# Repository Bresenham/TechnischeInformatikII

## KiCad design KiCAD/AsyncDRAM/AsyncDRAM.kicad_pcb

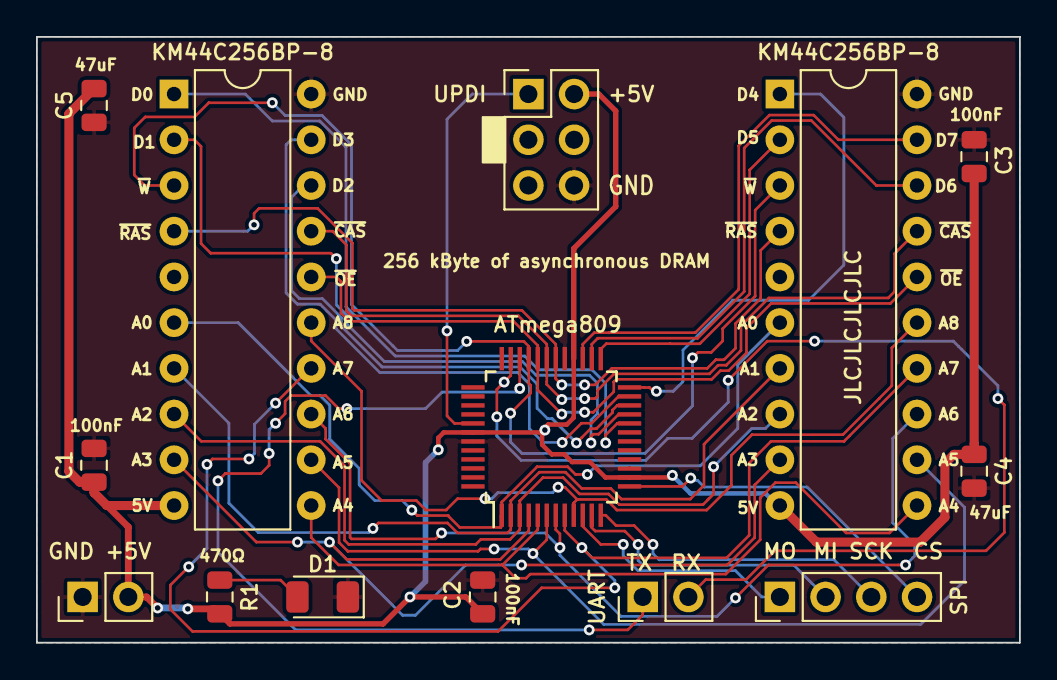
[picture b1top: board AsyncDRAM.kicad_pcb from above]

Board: 2 copper layers, 54.6 x 33.7 mm, 14 parts (0 on the bottom side), 31 nets.

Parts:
ATmega809: ATmega809; TQFP-48_7x7mm_P0.5mm
C1, C2, C3: 100nF; C_0805_2012Metric
C4, C5: 47µF; C_0805_2012Metric
D1: POWER_LED; LED_1206_3216Metric
J1: UART; PinHeader_1x02_P2.54mm_Vertical
J2: SPI; PinHeader_1x04_P2.54mm_Vertical
J3: UPDI; PinHeader_2x03_P2.54mm_Vertical
J4: POWER; PinHeader_1x02_P2.54mm_Vertical
KM44C256BP-8, KM44C256BP-8#2: KM44C256BP-8; DIP-20_W7.62mm
R1: 470Ohm; R_0805_2012Metric

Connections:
+5V: ATmega809.14, ATmega809.28, ATmega809.42, C1.1, C2.2, C3.2, C4.1, C5.2, J3.2, J4.2, KM44C256BP-8.10, KM44C256BP-8#2.10, R1.2
A0: ATmega809.1, KM44C256BP-8.6, KM44C256BP-8#2.6
A1: ATmega809.2, KM44C256BP-8.7, KM44C256BP-8#2.7
A2: ATmega809.3, KM44C256BP-8.8, KM44C256BP-8#2.8
A3: ATmega809.4, KM44C256BP-8.9, KM44C256BP-8#2.9
A4: ATmega809.5, KM44C256BP-8.11, KM44C256BP-8#2.11
A5: ATmega809.6, KM44C256BP-8.12, KM44C256BP-8#2.12
A6: ATmega809.7, KM44C256BP-8.13, KM44C256BP-8#2.13
A7: ATmega809.8, KM44C256BP-8.14, KM44C256BP-8#2.14
A8: ATmega809.9, KM44C256BP-8.15, KM44C256BP-8#2.15
D0: ATmega809.20, KM44C256BP-8.1
D1: ATmega809.21, KM44C256BP-8.2
D2: ATmega809.22, KM44C256BP-8.18
D3: ATmega809.23, KM44C256BP-8.19
D4: ATmega809.24, KM44C256BP-8#2.1
D5: ATmega809.25, KM44C256BP-8#2.2
D6: ATmega809.26, KM44C256BP-8#2.18
D7: ATmega809.27, KM44C256BP-8#2.19
GND: ATmega809.15, ATmega809.29, ATmega809.43, C1.2, C2.1, C3.1, C4.2, C5.1, D1.1, J3.6, J4.1, KM44C256BP-8.20, KM44C256BP-8#2.20
MISO: ATmega809.11, J2.2
MOSI: ATmega809.10, J2.1
unnamed: D1.2, R1.1
RxD: ATmega809.35, J1.2
SCK: ATmega809.12, J2.3
SS: ATmega809.13, J2.4
TxD: ATmega809.34, J1.1
UPDI: ATmega809.41, J3.1
~CAS: ATmega809.31, KM44C256BP-8.17, KM44C256BP-8#2.17
~OE: ATmega809.32, KM44C256BP-8.16, KM44C256BP-8#2.16
~RAS: ATmega809.30, KM44C256BP-8.4, KM44C256BP-8#2.4
~W: ATmega809.33, KM44C256BP-8.3, KM44C256BP-8#2.3

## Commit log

2019-10-18 Initial Commit KiCAD Project
2019-10-18 First Commit from ArchLinux Tablet
2019-10-18 Added Datasheet for possible µC, added QFP Footprints
2019-10-18 Library orga changed
2019-10-18 Relinked symbols
2019-10-19 Added ATmega809 Symbol
2019-10-19 Added Reference Manual, Advanced schematic design
2019-10-19 Advanced Schematic
2019-10-20 Added Library for SMD LEDs, updated PCB
2019-10-21 Adjusted Design Rules, added MT6205 BGA footprint for fun
2019-10-25 Finalizing schematic, adding TQFP footprint, PCB outline
2019-10-25 GND Planes
2019-10-25 Adjusted board settings to Elecrow Specifications
2019-10-26 Started PCB Routing...
2019-10-27 PCB Routing Update
2019-10-27 PCB Routing Bottom Half done
2019-10-27 Fixed LED finally
2019-10-27 Update PCB Routing
2019-10-27 Small PCB Routing Update
2019-10-31 Finished Routing PCB
2019-10-31 Beautify the Traces + Gerber Output
2019-11-01 Finalized silkscreen
2019-11-01 Re-routed power line from decoupling capacitor
2019-11-08 Added more silk screen
2019-11-10 Final Gerber Outputs for JLCPCB
2019-12-15 Added pictures
2019-12-20 Added IAR Project with some code
2019-12-22 Added Project for AtmelStudio
2019-12-22 Finally Timer0 Intr is working
2019-12-22 Implemented 'Read' and 'Write' DRAM2
2019-12-22 Minor change
2019-12-23 Added RAS-only refresh, fixed bug in 'writeByte'-function, added 'SPI-Init', added 'Buffer', defined commands for reading & writing
2019-12-23 SPI should be in SlaveMode
2019-12-24 Added Projectfiles for ESP8266 code, renamed AtmelStudio Project
2019-12-24 ESP8266 SPI seems to work now
2019-12-26 Update for today
2019-12-26 SPI seems to work now
2019-12-27 Updated IAR project, fixed stuff in ESP8266 and ATmega809 code
2019-12-27 Wifi HTTP Server Implementation
2019-12-29 FUCKING FUCKSHIT DOESN'T WORK
2019-12-29 Reading works! :)
2019-12-29 Added Writing webserver handler, added Mutex to synchronize SPIHandler with spi_event callback
2019-12-29 Finally, everything seems to work
2019-12-31 Added captures of SPI messages
2020-01-02 Added DRAM document
2020-01-02 Started presentation
2020-01-17 Added potential new 'Burst Read'-message to ATmega809
2020-01-17 Update Praesi
2020-01-25 Added Summary folder
2020-01-30 Update Presentation
2020-02-03 Last changes to presentation
